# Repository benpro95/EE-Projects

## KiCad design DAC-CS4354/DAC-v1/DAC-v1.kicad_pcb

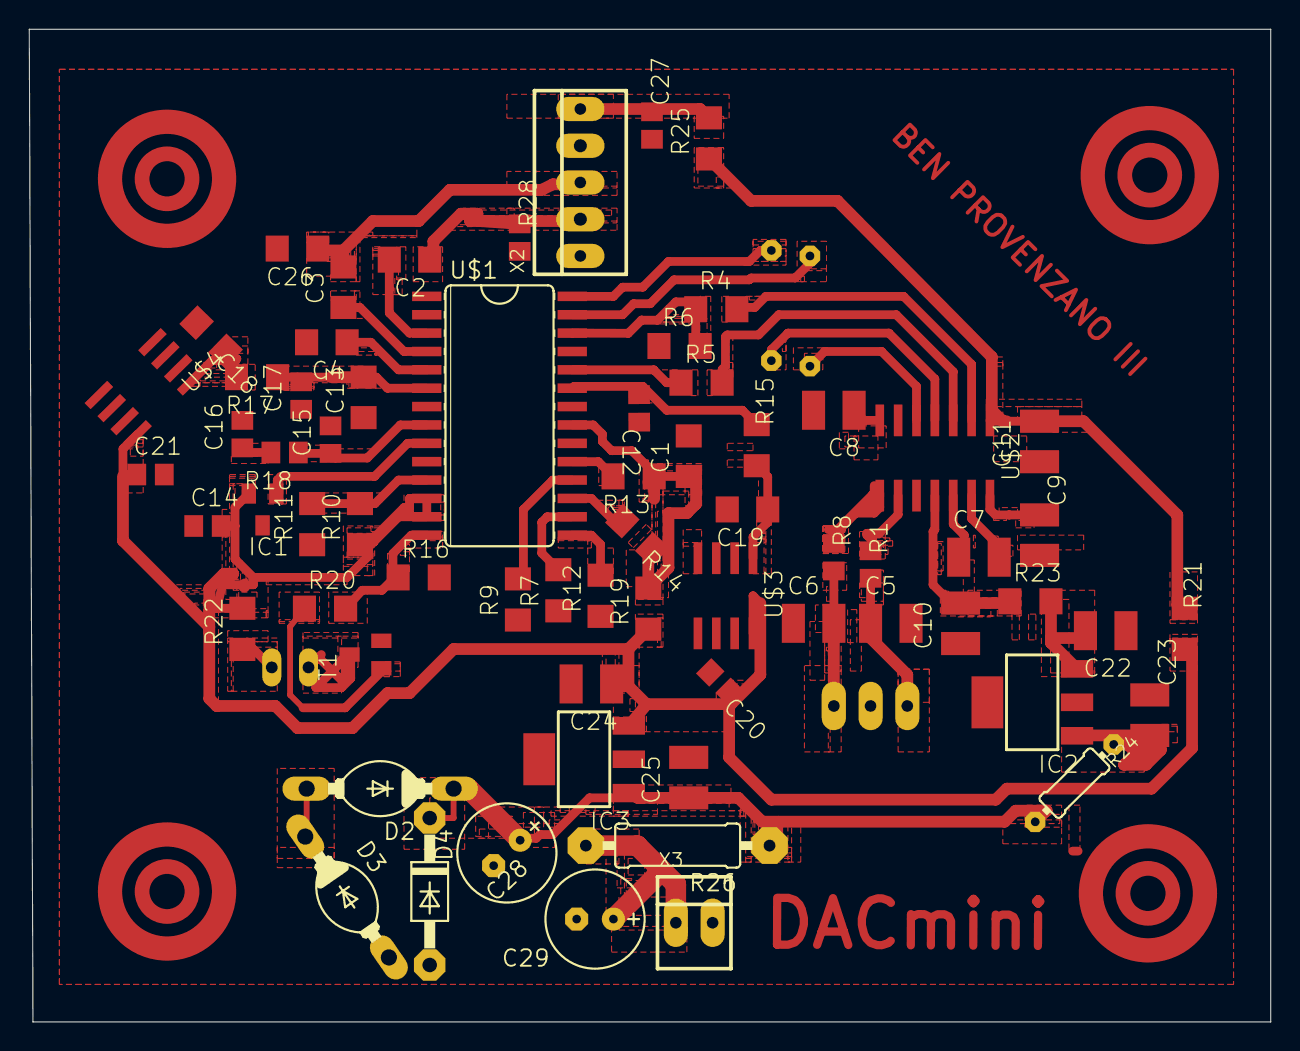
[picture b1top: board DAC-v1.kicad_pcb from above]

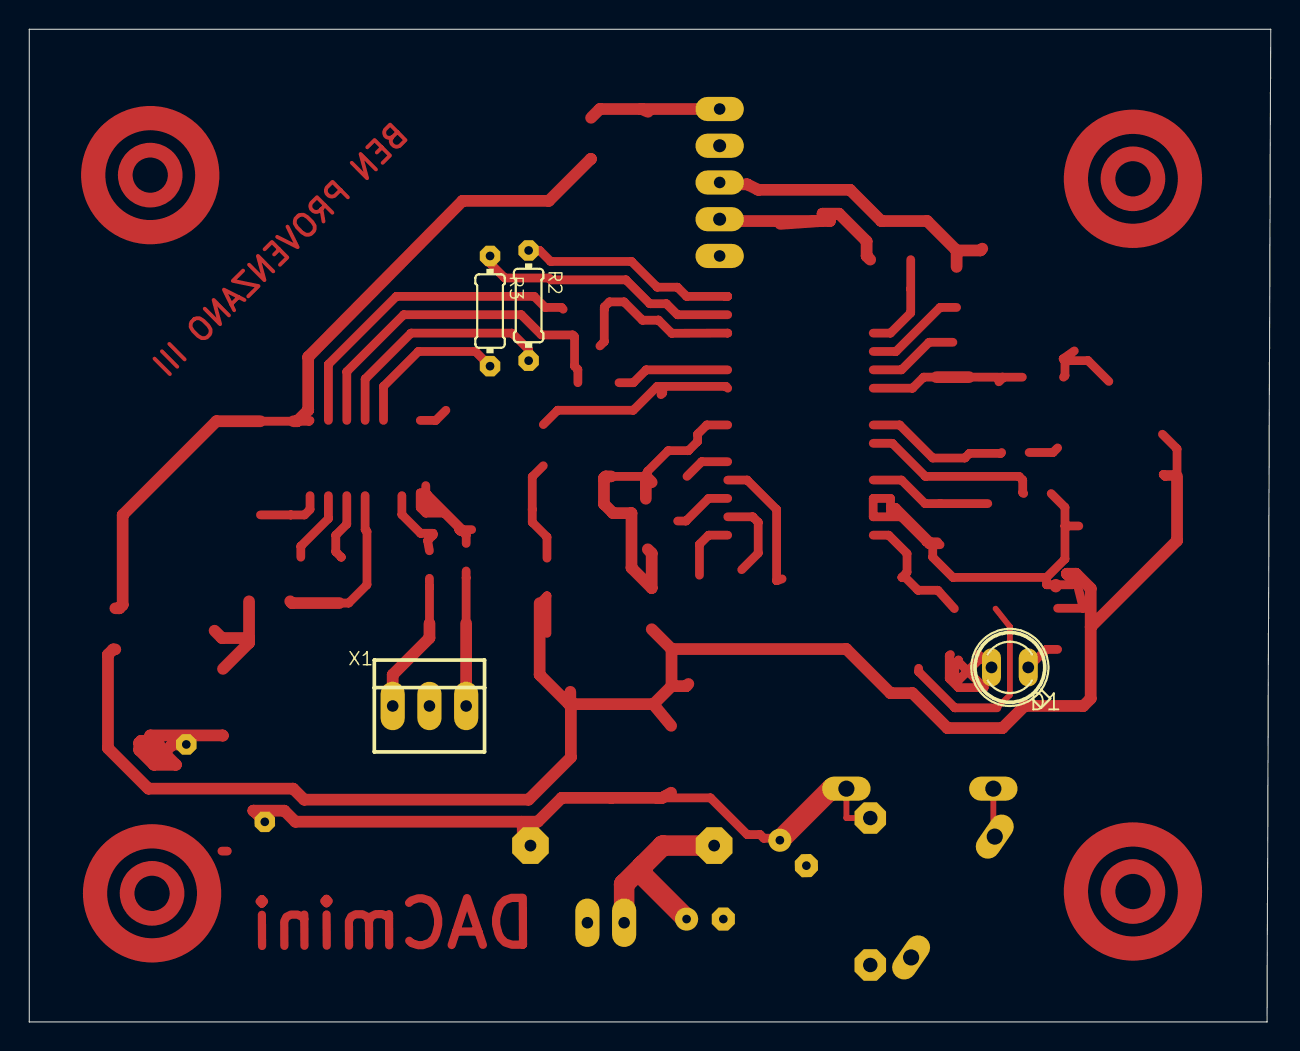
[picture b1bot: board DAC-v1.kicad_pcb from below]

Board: 2 copper layers, 85.8 x 68.6 mm, 71 parts (4 on the bottom side), 49 nets.

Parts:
C1: .1; C1206
C2, C3, C4: 10nF; C1206
C5, C6: 2n2; C1210
C7, C8, C9: 2u2; C1210
C10, C11, C23, C25: .1; C1210
C12, C14, C17, C20, C21, C27: .1; C0805
C13: 1nF; C1206
C15: 1nF; C0805
C16: 22nF; C0805
C18, C19: 10uF; C1206
C22, C24: 10u; C1210
C26: 30pF; C1206
C28, C29: 100uF; E2,5-7
D1: RED; SFH482
D2: 5V-TVS; DO204-10
D3: 8V5-TVS; DO204-10
D4: 1N4007; DO41-10
IC1: MCP130T-485; SOT23
IC2, IC3: LT1129-5; SOT223
R1, R8: 470R; R0805
R2, R3: 33R; 0204_7
R4, R5: 33R; R1206
R6, R7, R9, R12, R13, R14, R16, R20: 47k; R1206
R10: DNP; R1206
R11: 0; R1206
R15, R17, R19, R21, R23: FB; R1206
R18: 3k; R0805
R22: 2k2; R1206
R24: 0; 0204_7
R25: 47uH; R1206
R26: 10R; 0309_12
R28: 75; R0805
T1: BC846; SOT23
U$1: CS8416; SO28L
U$2: C4354; SO-14
U$3, U$4: LE33; SO-08
X1: AUDIO_OUT; 22-23-2031
X2: INPUT; 22-23-2051
X3: 12V; 22-23-2021

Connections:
GND: C1.2, C4.2, C5.2, C6.1, C8.2, C9.2, C10.1, C11.1, C12.1, C13.1, C14.1, C15.2, C16.2, C17.1, C18.2, C19.2, C20.2, C21.2, C22.1, C23.1, C24.2, C25.2, C26.2, C27.2, C28.-, C29.-, D3.A, D4.A, IC1.3, IC2.2, IC2.4, IC3.2, IC3.4, R6.1, R7.1, R9.1, R11.1, R12.1, R16.2, R28.2, T1.2, U$1.7, U$1.10, U$1.22, U$1.25, U$2.6, U$2.10, U$3.2, U$3.3, U$3.5, U$3.6, U$3.7, U$4.2, U$4.3, U$4.5, U$4.6, U$4.7, X1.2, X2.1, X2.4, X3.2
unnamed: IC1.1, U$1.9
unnamed: R4.1, R6.2, U$1.26
unnamed: C16.1, R18.2
unnamed: R5.1, U$1.24
unnamed: R3.1, U$1.27
unnamed: R2.1, U$1.28
unnamed: R2.2, U$2.4
unnamed: R3.2, U$2.5
unnamed: R4.2, U$2.2
unnamed: R5.2, U$2.3
unnamed: R7.2, U$1.16
unnamed: C3.1, U$1.4
unnamed: C2.2, U$1.3
unnamed: C4.1, U$1.5
unnamed: R1.1, U$2.9
unnamed: R8.1, U$2.8
unnamed: C5.1, R1.2, X1.1
unnamed: C6.2, R8.2, X1.3
unnamed: C13.2, C17.2, R17.1, U$1.6
unnamed: C7.2, U$2.13
unnamed: C7.1, U$2.12
unnamed: C9.1, U$2.14
unnamed: C8.1, U$2.7
unnamed: C12.2, R15.1, U$1.23
unnamed: C11.2, R21.1, R25.1, U$2.1
unnamed: C10.2, R23.1, U$2.11
unnamed: C1.1, R13.1, R14.1, R19.2, U$1.21
unnamed: R9.2, U$1.18
unnamed: R16.1, R20.2, U$1.14
unnamed: R10.2, R11.2, U$1.11
unnamed: C15.1, R18.1, U$1.8
unnamed: C22.2, IC2.3, R23.2
unnamed: C18.1, R17.2, U$4.1
unnamed: R12.2, U$1.15
unnamed: R13.2, U$1.19
unnamed: R14.2, U$1.17
unnamed: C19.1, R15.2, U$3.1
unnamed: R20.1, T1.1
unnamed: D1.K, T1.3
unnamed: D1.A, R22.1
unnamed: C29.+, R26.2, X3.1
unnamed: C14.2, C20.1, C21.1, C24.1, IC1.2, IC3.3, R10.1, R19.1, R21.2, R22.2, U$1.12, U$1.13, U$3.8, U$4.8
unnamed: C23.2, IC2.1, R24.1
unnamed: C3.2, C26.1, X2.3
unnamed: C25.1, C28.+, D2.C, D4.C, IC3.1, R24.2, R26.1
unnamed: C2.1, R28.1, X2.2
unnamed: C27.1, R25.2, X2.5
unnamed: D2.A, D3.C

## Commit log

2022-11-02 2022-11-01 20:56
2022-11-02 2022-11-01 21:02
2022-11-11 2022-11-11 09:03
2022-11-12 2022-11-11 21:16
2022-11-12 2022-11-12 04:21
2022-11-12 2022-11-12 15:55
2022-11-15 2022-11-15 06:53
2022-11-15 2022-11-15 07:15
2022-11-15 2022-11-15 07:43
2022-11-15 2022-11-15 15:15
2022-11-19 2022-11-19 05:00
2022-11-25 2022-11-25 17:01
2022-11-26 2022-11-26 00:18
2022-11-26 2022-11-26 00:36
2022-12-02 2022-12-01 20:45
2022-12-10 2022-12-10 09:39
2022-12-10 2022-12-10 13:26
2022-12-11 2022-12-11 12:42
2022-12-12 2022-12-12 06:13
2022-12-12 2022-12-12 13:30
2022-12-13 2022-12-13 07:53
2022-12-13 2022-12-13 17:40
2022-12-14 2022-12-13 22:49
2022-12-14 2022-12-14 13:45
2022-12-14 2022-12-14 15:57
2022-12-14 2022-12-14 16:08
2022-12-15 2022-12-15 14:08
2022-12-16 2022-12-15 19:37
2022-12-16 2022-12-15 23:06
2022-12-16 2022-12-16 06:18
2022-12-16 2022-12-16 10:49
2022-12-18 2022-12-17 22:41
2022-12-18 2022-12-18 00:52
2022-12-19 2022-12-18 21:59
2022-12-19 2022-12-19 15:05
2022-12-20 2022-12-19 22:24
2022-12-20 2022-12-19 22:54
2022-12-20 2022-12-19 23:31
2022-12-20 2022-12-20 10:03
2022-12-20 2022-12-20 11:06
2022-12-21 2022-12-21 06:55
2022-12-21 2022-12-21 12:03
2022-12-21 2022-12-21 17:01
2022-12-21 2022-12-21 17:14
2022-12-22 2022-12-21 20:03
2022-12-22 2022-12-21 21:08
2022-12-22 2022-12-21 21:27
2022-12-22 2022-12-21 21:28
2022-12-23 2022-12-23 09:33
2022-12-23 2022-12-23 14:15
2022-12-26 2022-12-25 19:55
2022-12-26 2022-12-26 11:24
2022-12-27 2022-12-27 11:16
2022-12-30 2022-12-30 08:26
2022-12-31 2022-12-31 07:51
2022-12-31 2022-12-31 08:42
2022-12-31 2022-12-31 10:10
2022-12-31 2022-12-31 11:21
2023-01-01 2022-12-31 20:19
2023-01-01 2023-01-01 06:55
2023-01-04 2023-01-04 05:10
2023-01-04 2023-01-04 07:08
2023-01-06 2023-01-06 01:57
2023-01-07 2023-01-07 05:01
2023-01-07 2023-01-07 17:03
2023-01-08 2023-01-07 19:43
2023-01-13 2023-01-13 06:34
2023-01-13 2023-01-13 06:47
2023-01-25 2023-01-25 05:36
2023-02-04 2023-02-03 23:56
2023-02-06 2023-02-06 11:32
2023-02-12 2023-02-12 08:04
2023-02-13 2023-02-13 14:56
2023-02-20 2023-02-20 11:50
2023-02-26 2023-02-26 17:27
2023-04-04 2023-04-03 20:28
2023-04-04 2023-04-03 20:30
2023-04-04 2023-04-03 21:24
2023-04-05 2023-04-04 21:51
2023-04-07 2023-04-07 15:28
2023-04-14 2023-04-13 21:15
2023-04-23 2023-04-22 21:32
2023-04-24 2023-04-24 11:49
2023-04-24 2023-04-24 12:02
2023-04-24 2023-04-24 12:31
2023-04-24 2023-04-24 14:15
2023-04-26 2023-04-25 20:33
2023-05-18 2023-05-17 21:27
2023-05-18 2023-05-18 08:48
2023-05-18 2023-05-18 08:49
2023-05-18 2023-05-18 19:05
2023-05-27 2023-05-27 09:22
2023-05-27 2023-05-27 09:26
2023-06-02 2023-06-02 04:45
2023-06-11 2023-06-10 22:36
2023-06-11 2023-06-10 22:46
2023-06-13 2023-06-12 20:24
2023-06-18 2023-06-17 22:12
2023-06-19 2023-06-18 22:30
2023-06-24 2023-06-23 20:52
2023-06-24 2023-06-24 10:19
2023-06-24 2023-06-24 10:24
2023-06-24 2023-06-24 16:25
2023-06-30 2023-06-30 07:35
2023-06-30 2023-06-30 17:09
2023-07-01 2023-06-30 23:40
2023-07-01 2023-07-01 00:55
2023-07-01 2023-07-01 09:48
2023-07-01 2023-07-01 11:25
2023-07-01 2023-07-01 19:52
2023-07-01 2023-07-01 19:58
2023-07-02 2023-07-02 07:32
2023-07-02 2023-07-02 19:44
2023-07-03 2023-07-02 20:09
2023-07-03 2023-07-02 20:20
2023-07-03 2023-07-02 21:17
2023-07-03 2023-07-02 21:25
2023-07-04 2023-07-04 08:37
2023-07-10 2023-07-09 23:06
2023-07-10 2023-07-10 07:45
2023-08-07 2023-08-06 21:44
2023-08-11 2023-08-10 21:30
2023-08-26 2023-08-26 06:57
2023-09-01 2023-09-01 06:12
2023-09-06 2023-09-05 20:45
2023-09-07 2023-09-06 21:05
2023-09-07 2023-09-06 22:15
2023-09-19 2023-09-19 18:16
2023-09-21 2023-09-21 19:33
2023-09-22 2023-09-22 14:25
2023-09-30 2023-09-30 15:44
2023-10-01 2023-10-01 11:25
2023-10-14 2023-10-14 10:54
2023-10-19 2023-10-18 20:15
2023-10-21 2023-10-21 06:40
2023-10-23 2023-10-23 18:07
2024-01-11 2024-01-10 21:24
2024-01-14 2024-01-13 20:14
2024-04-07 2024-04-06 21:56
2024-04-07 2024-04-07 00:16
2024-04-07 2024-04-07 11:08
2024-04-07 2024-04-07 11:44
2024-04-07 2024-04-07 12:03
2024-04-09 2024-04-08 21:35
2024-04-09 2024-04-08 21:54
2024-04-09 2024-04-08 22:01
2024-04-09 2024-04-09 19:52
2024-05-27 2024-05-27 19:51
2024-06-14 2024-06-13 21:57
2024-06-15 2024-06-15 10:49
2024-06-21 2024-06-21 19:56
2024-06-22 2024-06-21 21:47
2024-06-22 2024-06-21 22:34
2024-06-22 2024-06-21 22:52
2024-06-22 2024-06-21 22:55
2024-06-22 2024-06-22 09:12
2024-06-22 2024-06-22 09:40
2024-06-22 2024-06-22 10:55
2024-07-13 2024-07-13 19:47
2024-08-26 2024-08-26 07:41
2024-08-31 2024-08-30 23:14
2024-09-08 2024-09-08 11:19
2024-09-10 2024-09-10 14:36
2024-09-15 2024-09-15 11:05
2024-09-18 2024-09-17 20:09
2024-09-20 2024-09-20 16:12
2024-09-24 2024-09-23 22:43
2024-09-29 2024-09-29 14:28
2024-10-02 2024-10-02 16:38
2024-10-12 2024-10-11 23:13
2024-10-12 2024-10-12 11:04
2024-10-12 2024-10-12 19:05
2024-10-13 2024-10-12 20:30
2024-10-19 2024-10-19 09:18
2024-11-04 2024-11-04 07:28
2024-11-04 2024-11-04 11:21
2024-11-06 2024-11-05 20:22
2024-11-12 2024-11-12 13:19
2024-11-12 2024-11-12 18:07
2024-11-14 2024-11-14 18:48
2024-11-15 2024-11-15 16:50
2024-11-21 2024-11-20 21:36
2024-11-24 2024-11-23 21:17
2024-11-25 2024-11-24 20:44
2024-11-25 2024-11-25 08:14
2024-11-26 2024-11-25 21:29
2024-11-28 2024-11-28 10:20
2024-11-30 2024-11-30 18:47
2024-12-02 2024-12-02 14:49
2024-12-04 2024-12-03 21:38
2024-12-07 2024-12-07 17:53
2024-12-09 2024-12-08 22:26
